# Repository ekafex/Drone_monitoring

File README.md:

# Drone Atmospheric Monitoring Project 

This is an **R&D project funded by a AADF/READ grant** to build a **mobile atmospheric monitoring system** using a drone platform. The system architecture consists of **three measurement nodes**:

* **1 drone-mounted monitoring station**
* **1 fixed ground reference station**
* **1 mobile ground monitoring station** 

The drone platform is a **DJI Matrice 350 RTK**.

## Project Goal

Develop a **low-cost environmental monitoring system** capable of:

* mapping **air-pollution hotspots**
* performing **vertical atmospheric profiles**
* comparing drone measurements with **ground reference stations**

The system focuses on **relative air-quality indices rather than regulatory-grade concentrations**, to reduce integration complexity and cost.

## Sensor Strategy

Instead of multiple individual sensors (PM + gas + environmental), the system uses a **single integrated environmental node**:

**Primary sensor**

* **Sensirion SEN55**

    * PM1 / PM2.5 / PM4 / PM10
    * Temperature
    * Humidity
    * VOC index
    * NOx index
    * I²C interface

Advantages:

* factory calibrated
* digital output
* minimal analog electronics
* easier integration and maintenance

Optional upgrades discussed:

* **SCD4x CO₂ sensor**
* **SPS30 PM sensor for cross-validation**

## Electronics Architecture

Each station uses the same electronics design.

Core components:

**Microcontroller**

* ESP32-S3-DevKitC-1U development board

**Positioning**

* u-blox NEO-M9N GNSS module

**Communication**

* LoRa (868 MHz) telemetry

**Data storage**

* microSD logging

**Power**

* LiPo battery (drone/mobile)
* DC-DC regulators

## Communication Architecture

Telemetry uses **point-to-point LoRa (868 MHz)**.

Structure:

Drone node
→ LoRa
→ Ground station receiver

A LoRaWAN gateway is optional for later expansion.

## Airflow and Sensor Placement

Drone airflow strongly affects measurements.

Recommended design:

* **Side boom mounting**
* sensor inlet placed **~0.7–1.0 m from drone center**
* **aspirated sampling inlet** using a small fan
* **short inlet tubing**

This minimizes rotor downwash interference.

## Calibration Strategy

Because the system uses **relative air-quality indices**, calibration relies on **co-location** instead of expensive gas calibrators.

Procedure:

1. Run all stations **side-by-side for 1–2 weeks**
2. Compare sensor outputs
3. derive correction factors
4. validate against any available **reference station**

Industrial calibration devices exist but are **too expensive** for this project.

## Flight Sampling Protocol

Recommended drone measurement strategy:

1. Fly to location
2. **hover sampling segments (10–30 s)**
3. move to next point
4. repeat

Avoid measuring during rapid motion.

Use:

* vertical profiles
* grid sampling
* repeated transects

## System Deployment

Final system will include:

**Drone station**

* SEN55
* ESP32
* GNSS
* LoRa
* microSD
* aspirated inlet

**Fixed ground station**

* same sensors
* weatherproof enclosure
* continuous operation

**Mobile ground station**

* same hardware
* portable enclosure

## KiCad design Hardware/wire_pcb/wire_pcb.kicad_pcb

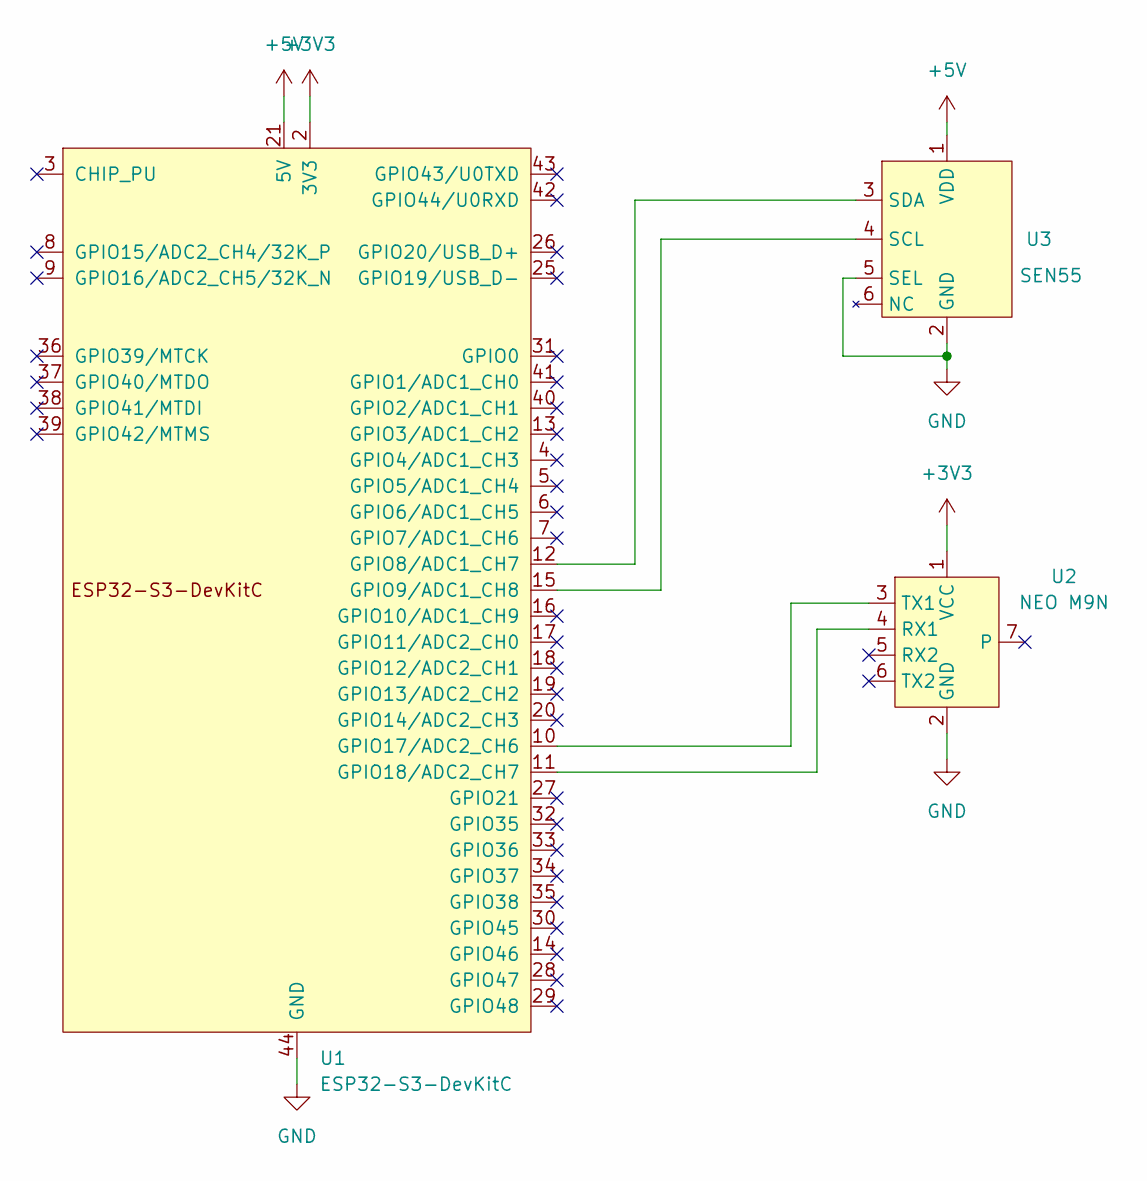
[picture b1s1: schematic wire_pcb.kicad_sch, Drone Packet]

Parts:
U1: ESP32-S3-DevKitC
U2: NEO M9N
U3: SEN55

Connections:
+3V3: U1.1 (3V3), U1.2 (3V3), U2.1 (VCC)
+5V: U1.21 (5V), U3.1 (VDD)
GND: U1.22 (GND), U1.23 (GND), U1.24 (GND), U1.44 (GND), U2.2 (GND), U3.2 (GND), U3.5 (SEL)
unnamed: U1.12 (GPIO8/ADC1_CH7), U3.3 (SDA)
unnamed: U1.15 (GPIO9/ADC1_CH8), U3.4 (SCL)
unnamed: U1.10 (GPIO17/ADC2_CH6), U2.3 (TX1)
unnamed: U1.11 (GPIO18/ADC2_CH7), U2.4 (RX1)

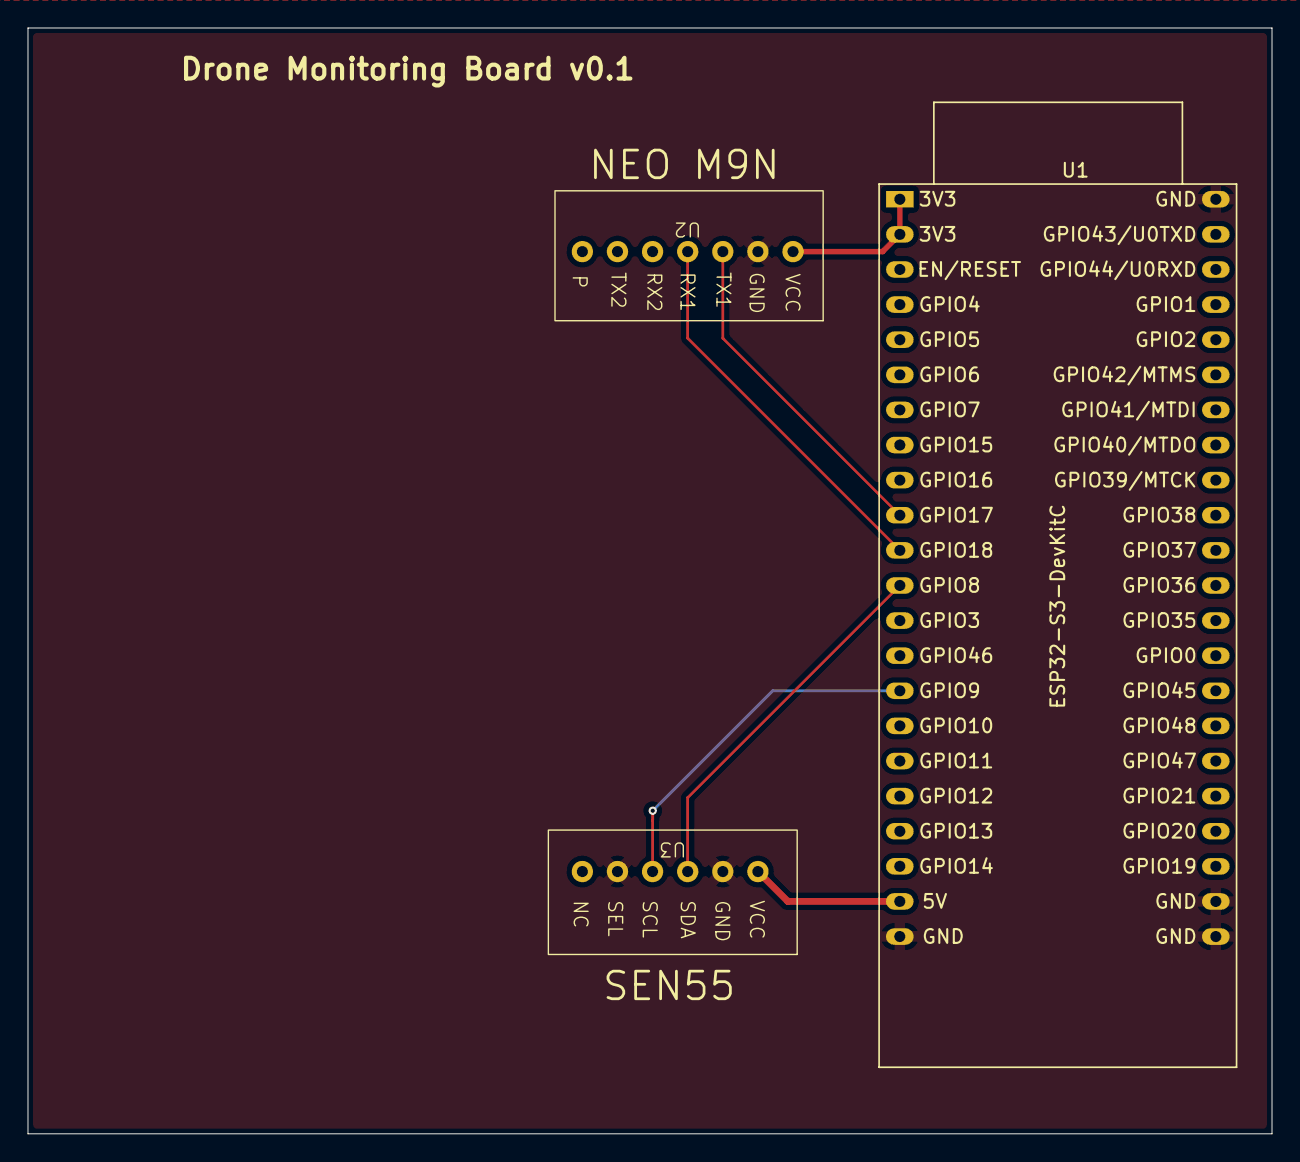
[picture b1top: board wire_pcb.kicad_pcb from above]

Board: 2 copper layers, 90.0 x 80.0 mm, 3 parts (0 on the bottom side), 7 nets.

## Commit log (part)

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2026-05-30 Added some sensor information + first firmware for reading data from SEN55 sensor
2026-05-31 Updated firmware and documentation
2026-06-01 Updated Firmware/src/main.cpp to include GNSS + SEN55 together and uodated Firmware/platformio.ini
2026-06-02 Updated documentation
2026-06-07 added presentation at Doc/Presentations/group_meeting_07_06_2026.pdf
2026-06-09 Added presentation for the school Doc/Presentations/school_10_06_2026.pdf
2026-06-16 MCA connection gamma-ray scintillator detector
2026-06-20 Added meeting file list
2026-06-20 Updaed date of meeting file Doc/Meetings/Meetings.md
2026-06-23 Add initial for Gerti in meetings table
2026-06-24 updated Firmware Firmware/src/main.cpp, also change meetin report
2026-06-28 Created Hardware folder and add first version of the wiring and PCB using KiCAD 10
